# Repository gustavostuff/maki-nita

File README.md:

MakiNeat is a cartridge-based, two-player portable tabletop Arcade. The name comes from _maquinita_ (pronounced very similarly), the Mexican word generally used for an arcade machine. The display is four white 8x8 LED matrices in a 16x16 field. Graphics are 1-bit (LEDs are either ON or OFF).

On a similar spirit as the Magnavox Odyssey and the Vectrex, MakiNeat uses colored, translucent sheets to cover the screen. So the overlay is an extension of the cartridge, part of the game experience. A magnetic marquee runs along the top and the cartridge sits behind it. The [overlays](docs/overlays.md) and [design](docs/design.md) docs cover the sheet and the system netlist.

An AVR128DB28 on a cartridge runs the game and holds the picture (the cartridge is both the system brain and the game data). Four MAX7219 drivers refresh the screen grid.

## Goals

Simple graphics + simple input can still be fun. A stick (and sometimes a button) is all that's needed. Together with cartridges, colored overlays, and a sturdy design, that is the spirit of MakiNeat.

The build is a simple soldering job.

- Parts are through-hole, on a 2.54 mm grid.
- Chips sit in sockets, so a bad one can be swapped.
- Wires leave the board on headers. Two for player controls, another one for power/reset, and one more for the speaker.

Parts are cheap.

- The main system board is a two-layer 100x100 mm board (~5 USD + shipping). The cartridge is an even smaller PCB.
- The screen is four white 8x8 LED matrices (normally less than 1 USD each), and the chips are commonly available (not EOL or NRND).

- Power is any generic/regulated 5 V adapter.

Software is under the MIT License. The hardware design is under the CERN Open Hardware Licence Version 2, Strongly Reciprocal.

## PCBs

Copper tracing is still a WIP for the main PCB, but the full [SKiDL netlist](tools/kicad/main-pcb/skidl/makineat.py) and KiCad files are already under `tools/kicad/main-pcb/` and `tools/kicad/cart-pcb/` (not tested IRL).

Main system PCB, 100x100 mm:

Cartridge PCB, 44x37 mm:

## Game simulator

`tools/sim` is a netlist simulation of the system. The simulator compiles the cartridge's C game code natively on the host to drive the hardware model. This same C code can be directly flashed to the AVR on the cartridge.

SKiDL export writes `tools/kicad/main-pcb/skidl/makineat.net` and updates net classes in `tools/kicad/main-pcb/makineat_v_04.kicad_pro`. See [firmware](docs/firmware.md).

`./sim.sh` opens the UI. The active cart is named in `cart_placed.json`.

## Screen overlay

Physical translucent sheets, placed in front of the white matrix LEDs and status digits, make multi-colored graphics. A single framed overlay holds colored acetate cutouts across both zones, with game labels along the frame:

## Docs

- [Design](docs/design.md) is the system netlist, cart edge, display chain, and audio wiring from SKiDL and KiCad.
- [Firmware](docs/firmware.md) is the game loop, inputs, sound, SDK, and simulator.
- [Overlays](docs/overlays.md) is the colored sheet in front of the field.
- [Future plans](docs/future-plans.md) is the hardware and firmware enhancement roadmap.
- [Status digits](docs/status-digits.md) is the fifth driver and 7-segment display proposal.
- [Driver to matrix pinout](docs/driver_to_matrix_pinout.md) is the MAX7219 and 1088AS LED matrix pinout and activation reference.

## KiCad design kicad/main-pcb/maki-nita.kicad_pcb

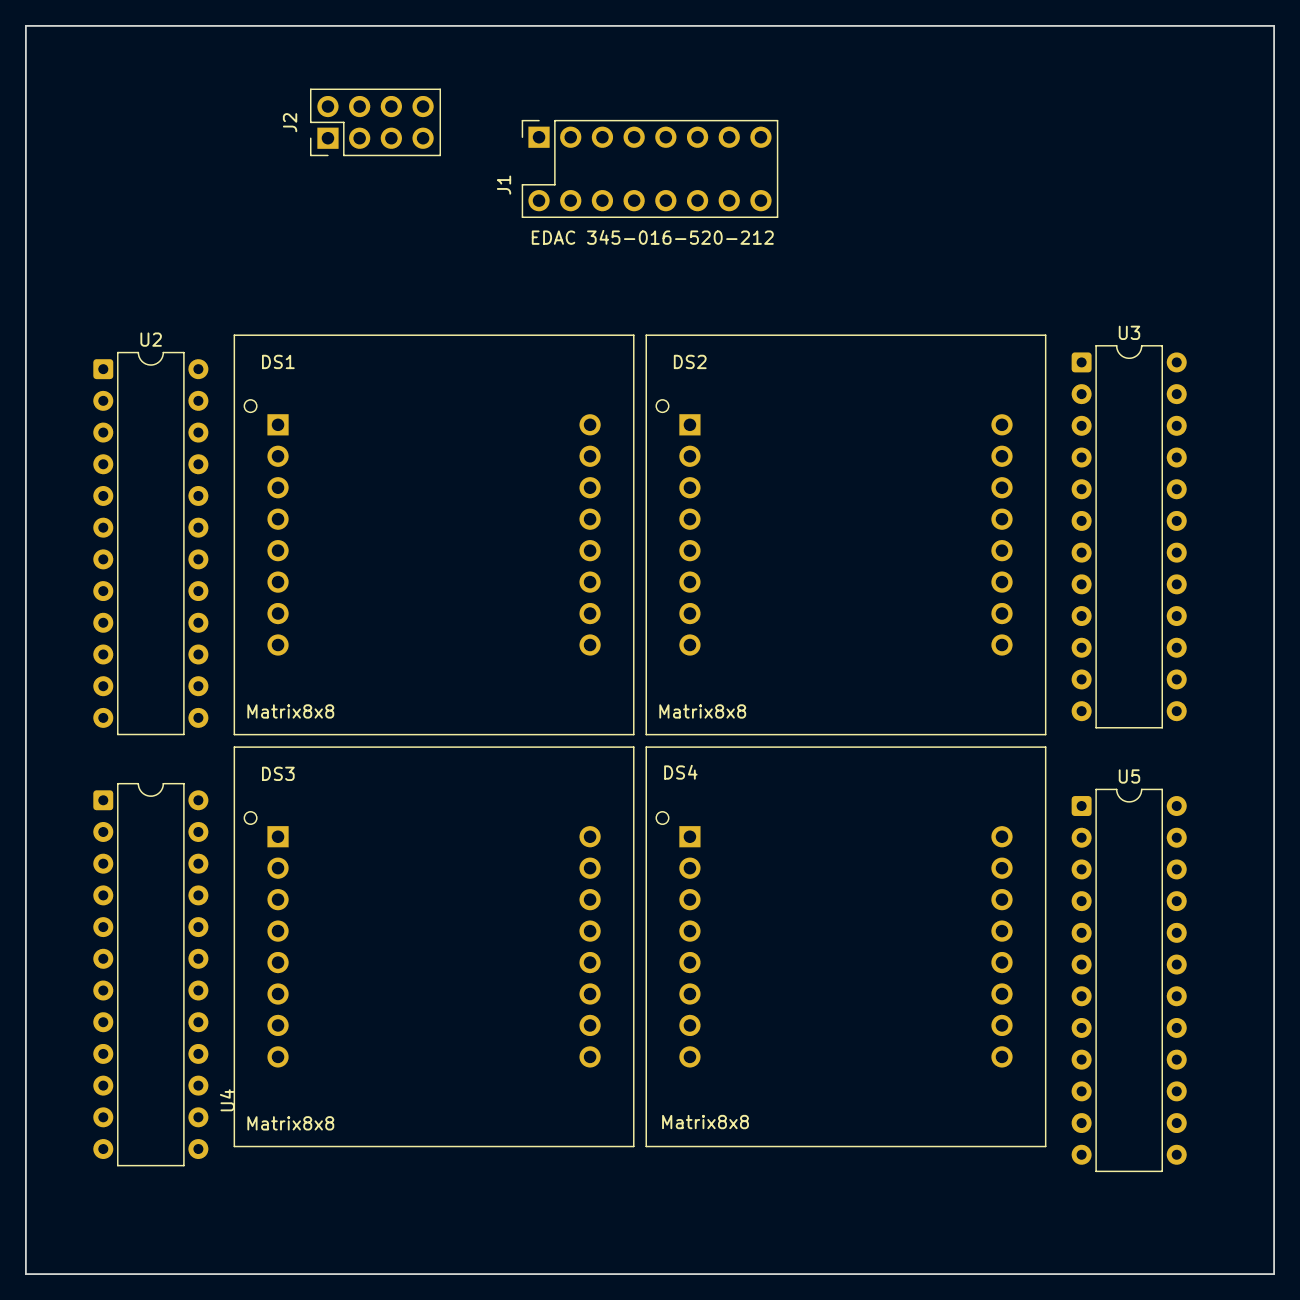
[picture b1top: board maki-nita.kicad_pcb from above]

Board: 2 copper layers, 100.0 x 100.0 mm, 10 parts (0 on the bottom side), 77 nets, no tracks yet.

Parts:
DS1, DS2, DS3, DS4: Matrix8x8; Matrix8x8_2x8_P2.52mm_R25mm
J1: EDAC 345-016-520-212; EDAC_345_MoboSocket_2x8_2.54x5.08mm
J2: PinHeader 2x04; PinHeader_2x04_P2.54mm_Vertical
U2, U3, U4, U5: MAX7219; DIP-24_W7.62mm

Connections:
+5V: J1.3, J1.4, J1.16, J2.2, U2.19, U3.19, U4.19, U5.19
BUTTON: J1.13, J2.7
CLK: J1.10, U2.13, U3.13, U4.13, U5.13
DIN: J1.8, U2.1
DOUT_U2: U2.24, U3.1
DOUT_U3: U3.24, U4.1
DOUT_U4: U4.24, U5.1
DOWN: J1.7, J2.4
GND: J1.1, J1.2, J1.15, J2.1, J2.8, U2.4, U2.9, U3.4, U3.9, U4.4, U4.9, U5.4, U5.9
LEFT: J1.9, J2.5
LOAD: J1.6, U2.12, U3.12, U4.12, U5.12
RIGHT: J1.11, J2.6
ROW1_DS1_C0: DS1.1, U2.22
ROW1_DS1_C1: DS1.2, U2.14
ROW1_DS1_C2: DS1.3, U2.16
ROW1_DS1_C3: DS1.4, U2.20
ROW1_DS1_C4: DS1.5, U2.23
ROW1_DS1_C5: DS1.6, U2.21
ROW1_DS1_C6: DS1.7, U2.15
ROW1_DS1_C7: DS1.8, U2.17
ROW1_DS1_R0: DS1.16, U2.2
ROW1_DS1_R1: DS1.15, U2.11
ROW1_DS1_R2: DS1.14, U2.6
ROW1_DS1_R3: DS1.13, U2.7
ROW1_DS1_R4: DS1.12, U2.3
ROW1_DS1_R5: DS1.11, U2.10
ROW1_DS1_R6: DS1.10, U2.5
ROW1_DS1_R7: DS1.9, U2.8
ROW1_DS2_C0: DS2.1, U3.22
ROW1_DS2_C1: DS2.2, U3.14
ROW1_DS2_C2: DS2.3, U3.16
ROW1_DS2_C3: DS2.4, U3.20
ROW1_DS2_C4: DS2.5, U3.23
ROW1_DS2_C5: DS2.6, U3.21
ROW1_DS2_C6: DS2.7, U3.15
ROW1_DS2_C7: DS2.8, U3.17
ROW1_DS2_R0: DS2.16, U3.2
ROW1_DS2_R1: DS2.15, U3.11
ROW1_DS2_R2: DS2.14, U3.6
ROW1_DS2_R3: DS2.13, U3.7
ROW1_DS2_R4: DS2.12, U3.3
ROW1_DS2_R5: DS2.11, U3.10
ROW1_DS2_R6: DS2.10, U3.5
ROW1_DS2_R7: DS2.9, U3.8
ROW2_DS3_C0: DS3.1, U4.22
ROW2_DS3_C1: DS3.2, U4.14
ROW2_DS3_C2: DS3.3, U4.16
ROW2_DS3_C3: DS3.4, U4.20
ROW2_DS3_C4: DS3.5, U4.23
ROW2_DS3_C5: DS3.6, U4.21
ROW2_DS3_C6: DS3.7, U4.15
ROW2_DS3_C7: DS3.8, U4.17
ROW2_DS3_R0: DS3.16, U4.2
ROW2_DS3_R1: DS3.15, U4.11
ROW2_DS3_R2: DS3.14, U4.6
ROW2_DS3_R3: DS3.13, U4.7
ROW2_DS3_R4: DS3.12, U4.3
ROW2_DS3_R5: DS3.11, U4.10
ROW2_DS3_R6: DS3.10, U4.5
ROW2_DS3_R7: DS3.9, U4.8
ROW2_DS4_C0: DS4.1, U5.22
ROW2_DS4_C1: DS4.2, U5.14
ROW2_DS4_C2: DS4.3, U5.16
ROW2_DS4_C3: DS4.4, U5.20
ROW2_DS4_C4: DS4.5, U5.23
ROW2_DS4_C5: DS4.6, U5.21
ROW2_DS4_C6: DS4.7, U5.15
ROW2_DS4_C7: DS4.8, U5.17
ROW2_DS4_R0: DS4.16, U5.2
ROW2_DS4_R1: DS4.15, U5.11
ROW2_DS4_R2: DS4.14, U5.6
ROW2_DS4_R3: DS4.13, U5.7
ROW2_DS4_R4: DS4.12, U5.3
ROW2_DS4_R5: DS4.11, U5.10
ROW2_DS4_R6: DS4.10, U5.5
ROW2_DS4_R7: DS4.9, U5.8
UP: J1.5, J2.3

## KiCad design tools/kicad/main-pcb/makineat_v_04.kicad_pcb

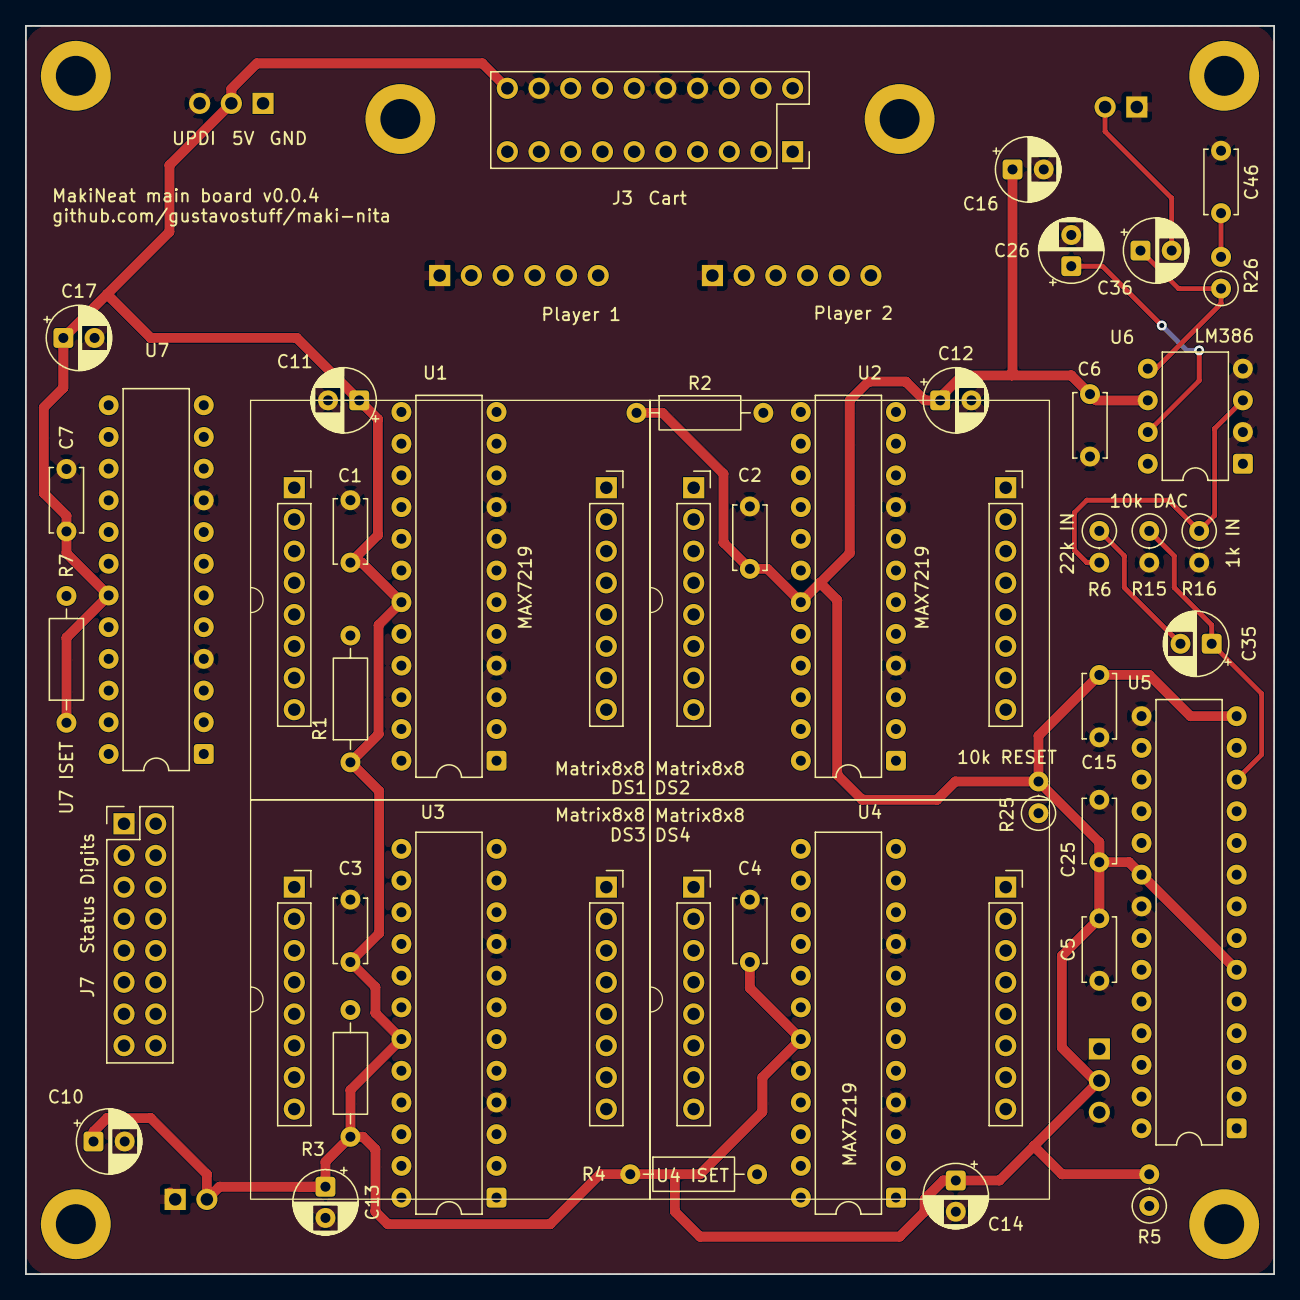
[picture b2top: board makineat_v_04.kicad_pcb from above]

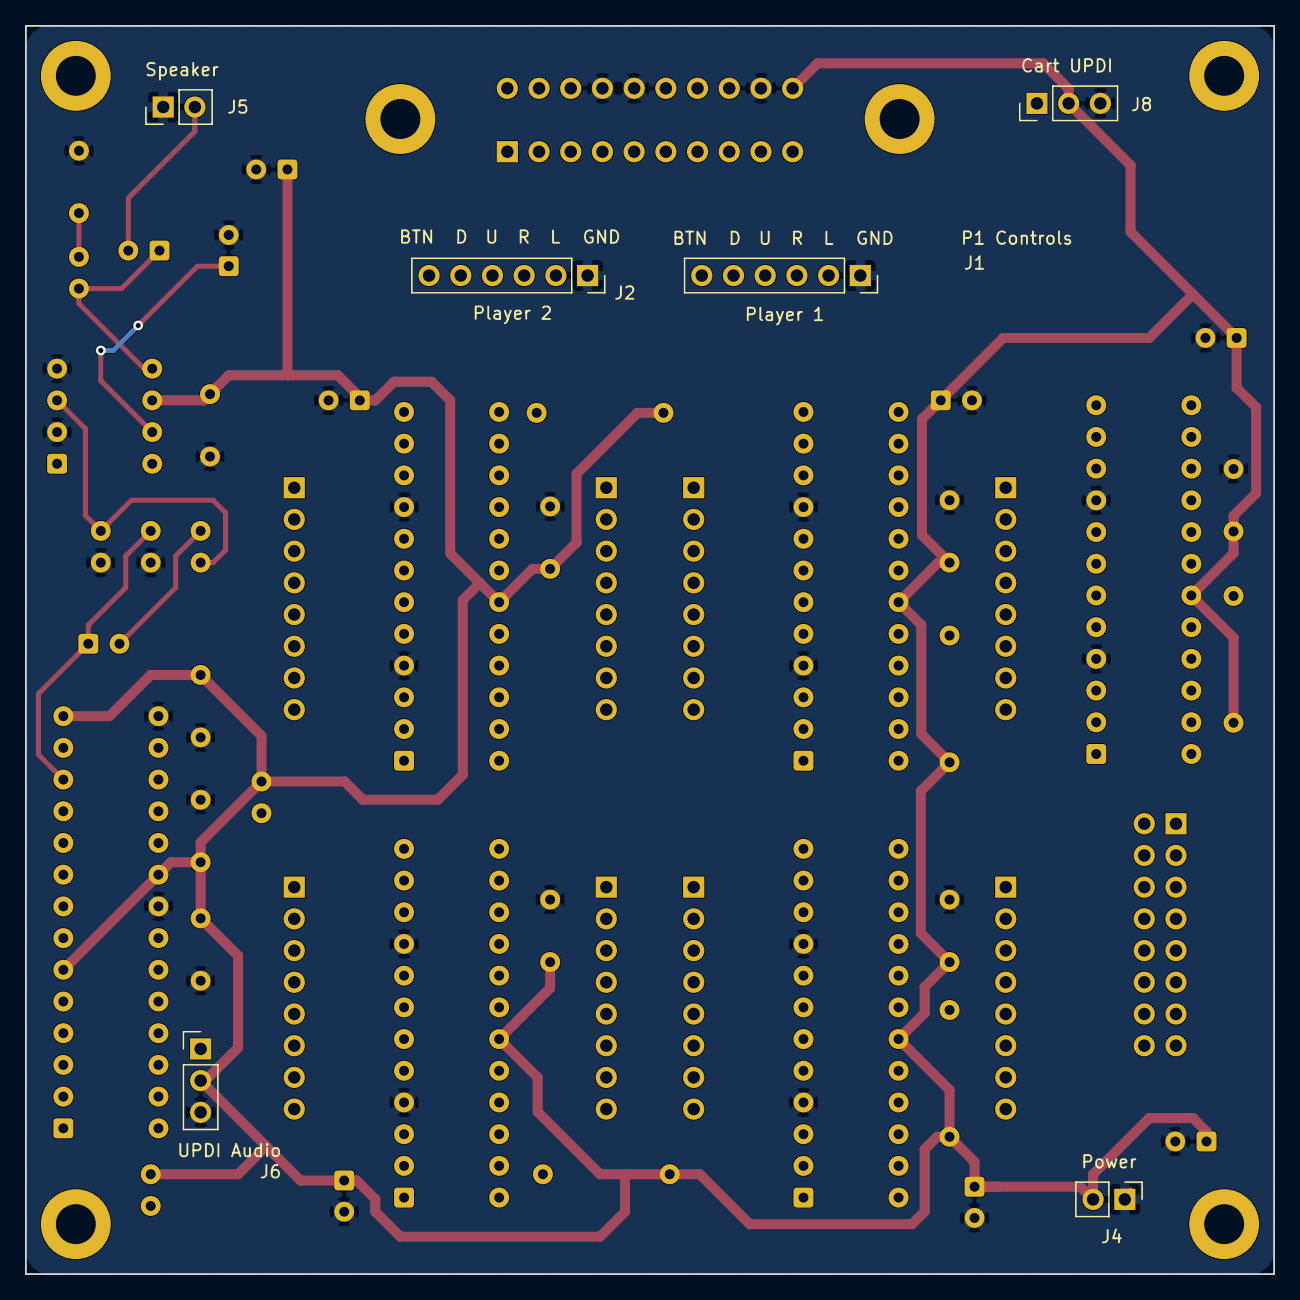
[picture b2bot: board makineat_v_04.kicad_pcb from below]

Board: 2 copper layers, 100.0 x 100.0 mm, 50 parts (6 on the bottom side), 115 nets.

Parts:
C1: U1 V+; C_Disc_D5.0mm_W2.5mm_P5.00mm
C2: U2 V+; C_Disc_D5.0mm_W2.5mm_P5.00mm
C3: U3 V+; C_Disc_D5.0mm_W2.5mm_P5.00mm
C4: U4 V+; C_Disc_D5.0mm_W2.5mm_P5.00mm
C5: U5 VDD; C_Disc_D5.0mm_W2.5mm_P5.00mm
C6: U6 VS; C_Disc_D5.0mm_W2.5mm_P5.00mm
C7: U7 V+; C_Disc_D5.0mm_W2.5mm_P5.00mm
C10: 470u VCC; CP_Radial_D5.0mm_P2.50mm
C11: U1 10u; CP_Radial_D5.0mm_P2.50mm
C12: U2 10u; CP_Radial_D5.0mm_P2.50mm
C13: U3 10u; CP_Radial_D5.0mm_P2.50mm
C14: U4 10u; CP_Radial_D5.0mm_P2.50mm
C15: U5 AVDD; C_Disc_D5.0mm_W2.5mm_P5.00mm
C16: U6 VS; CP_Radial_D5.0mm_P2.50mm
C17: U7 10u; CP_Radial_D5.0mm_P2.50mm
C25: U5 IO; C_Disc_D5.0mm_W2.5mm_P5.00mm
C26: U6 BYP; CP_Radial_D5.0mm_P2.50mm
C35: 1u DAC; CP_Radial_D5.0mm_P2.50mm
C36: 220u SPK; CP_Radial_D5.0mm_P2.50mm
C46: 47n ZOB; C_Disc_D5.0mm_W2.5mm_P5.00mm
DS1, DS2, DS3, DS4: Matrix8x8; Matrix8x8_2x8_P2.52mm_R25mm
J1: P1 Controls; PinHeader_1x06_P2.54mm_Vertical
J2: P2 Controls; PinHeader_1x06_P2.54mm_Vertical
J3: Cart; EDAC_395_MoboSocket_2x10_2.54x5.08mm
J4: Power; PinHeader_1x02_P2.54mm_Vertical
J5: Speaker; PinHeader_1x02_P2.54mm_Vertical
J6: UPDI Audio; PinHeader_1x03_P2.54mm_Vertical
J7: Status Digits; PinHeader_2x08_P2.54mm_Vertical
J8: Cart UPDI; PinHeader_1x03_P2.54mm_Vertical
R1: U1 ISET; R_Axial_DIN0207_L6.3mm_D2.5mm_P10.16mm_Horizontal
R2: U2 ISET; R_Axial_DIN0207_L6.3mm_D2.5mm_P10.16mm_Horizontal
R3: U3 ISET; R_Axial_DIN0207_L6.3mm_D2.5mm_P10.16mm_Horizontal
R4: U4 ISET; R_Axial_DIN0207_L6.3mm_D2.5mm_P10.16mm_Horizontal
R5: 10k EVENT; R_Axial_DIN0207_L6.3mm_D2.5mm_P2.54mm_Vertical
R6: 22k IN; R_Axial_DIN0207_L6.3mm_D2.5mm_P2.54mm_Vertical
R7: U7 ISET; R_Axial_DIN0207_L6.3mm_D2.5mm_P10.16mm_Horizontal
R15: 10k DAC; R_Axial_DIN0207_L6.3mm_D2.5mm_P2.54mm_Vertical
R16: 1k IN; R_Axial_DIN0207_L6.3mm_D2.5mm_P2.54mm_Vertical
R25: 10k RESET; R_Axial_DIN0207_L6.3mm_D2.5mm_P2.54mm_Vertical
R26: 10R ZOB; R_Axial_DIN0207_L6.3mm_D2.5mm_P2.54mm_Vertical
U1, U2, U3, U4, U7: MAX7219; DIP-24_W7.62mm
U5: Audio AVR; DIP-28_W7.62mm
U6: LM386; DIP-8_W7.62mm

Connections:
+5V: C1.1, C2.1, C3.1, C4.1, C5.1, C6.1, C7.1, C10.1, C11.1, C12.1, C13.1, C14.1, C15.1, C16.1, C17.1, C25.1, J3.20, J4.2, J6.2, J8.2, R1.1, R2.1, R3.1, R4.1, R5.2, R7.1, R25.2, U1.19, U2.19, U3.19, U4.19, U5.6, U5.14, U5.20, U6.6, U7.19
AMP: C36.1, R26.1, U6.5
AUD: C35.2, R6.1
AUDIN: R6.2, R16.1, U6.3
AUDIO_UPDI: J6.1, U5.19
BYPASS: C26.1, U6.7
CLK: J3.2, U1.13, U2.13, U3.13, U4.13, U7.13
DAC: C35.1, R15.1, U5.12
DIN: J3.6, U1.1
DOUT_U1: U1.24, U2.1
DOUT_U2: U2.24, U3.1
DOUT_U3: U3.24, U4.1
DOUT_U4: U4.24, U7.1
DS1_0: DS1.0, U1.17
DS1_1: DS1.1, U1.15
DS1_2: DS1.2, U1.11
DS1_3: DS1.3, U1.22
DS1_4: DS1.4, U1.7
DS1_5: DS1.5, U1.21
DS1_6: DS1.6, U1.20
DS1_7: DS1.7, U1.2
DS1_8: DS1.8, U1.3
DS1_9: DS1.9, U1.5
DS1_A: DS1.A, U1.14
DS1_B: DS1.B, U1.16
DS1_C: DS1.C, U1.8
DS1_D: DS1.D, U1.23
DS1_E: DS1.E, U1.10
DS1_F: DS1.F, U1.6
DS2_0: DS2.0, U2.17
DS2_1: DS2.1, U2.15
DS2_2: DS2.2, U2.11
DS2_3: DS2.3, U2.22
DS2_4: DS2.4, U2.7
DS2_5: DS2.5, U2.21
DS2_6: DS2.6, U2.20
DS2_7: DS2.7, U2.2
DS2_8: DS2.8, U2.3
DS2_9: DS2.9, U2.5
DS2_A: DS2.A, U2.14
DS2_B: DS2.B, U2.16
DS2_C: DS2.C, U2.8
DS2_D: DS2.D, U2.23
DS2_E: DS2.E, U2.10
DS2_F: DS2.F, U2.6
DS3_0: DS3.0, U3.17
DS3_1: DS3.1, U3.15
DS3_2: DS3.2, U3.11
DS3_3: DS3.3, U3.22
DS3_4: DS3.4, U3.7
DS3_5: DS3.5, U3.21
DS3_6: DS3.6, U3.20
DS3_7: DS3.7, U3.2
DS3_8: DS3.8, U3.3
DS3_9: DS3.9, U3.5
DS3_A: DS3.A, U3.14
DS3_B: DS3.B, U3.16
DS3_C: DS3.C, U3.8
DS3_D: DS3.D, U3.23
DS3_E: DS3.E, U3.10
DS3_F: DS3.F, U3.6
DS4_0: DS4.0, U4.17
DS4_1: DS4.1, U4.15
DS4_2: DS4.2, U4.11
DS4_3: DS4.3, U4.22
DS4_4: DS4.4, U4.7
DS4_5: DS4.5, U4.21
DS4_6: DS4.6, U4.20
DS4_7: DS4.7, U4.2
DS4_8: DS4.8, U4.3
DS4_9: DS4.9, U4.5
DS4_A: DS4.A, U4.14
DS4_B: DS4.B, U4.16
DS4_C: DS4.C, U4.8
DS4_D: DS4.D, U4.23
DS4_E: DS4.E, U4.10
DS4_F: DS4.F, U4.6
DS5_0: J7.1, U7.17
DS5_1: J7.2, U7.15
DS5_2: J7.3, U7.11
DS5_3: J7.4, U7.22
DS5_4: J7.9, U7.7
DS5_5: J7.10, U7.21
DS5_6: J7.11, U7.20
DS5_7: J7.12, U7.2
DS5_8: J7.5, U7.3
DS5_9: J7.6, U7.5
DS5_A: J7.7, U7.14
DS5_B: J7.8, U7.16
DS5_C: J7.13, U7.8
DS5_D: J7.14, U7.23
DS5_E: J7.15, U7.10
DS5_F: J7.16, U7.6
EVENT: J3.16, R5.1, U5.23
GND: C1.2, C2.2, C3.2, C4.2, C5.2, C6.2, C7.2, C10.2, C11.2, C12.2, C13.2, C14.2, C15.2, C16.2, C17.2, C25.2, C26.2, C46.2, J1.1, J2.1, J3.8, J3.10, J3.18, J4.1, J5.1, J6.3, J8.3, R15.2, R16.2, U1.4, U1.9, U2.4, U2.9, U3.4, U3.9, U4.4, U4.9, U5.15, U5.21, U6.2, U6.4, U7.4, U7.9
LOAD: J3.4, U1.12, U2.12, U3.12, U4.12, U7.12
P1_BTN: J1.6, J3.11
P1_DOWN: J1.5, J3.13
P1_LEFT: J1.2, J3.19
P1_RIGHT: J1.3, J3.17
P1_UP: J1.4, J3.15
P2_BTN: J2.6, J3.1
P2_DOWN: J2.5, J3.3
P2_LEFT: J2.2, J3.9
P2_RIGHT: J2.3, J3.7
P2_UP: J2.4, J3.5
RESET: J3.14, R25.1, U5.18
SPK: C36.2, J5.2
U1_ISET: R1.2, U1.18
U2_ISET: R2.2, U2.18
U3_ISET: R3.2, U3.18
U4_ISET: R4.2, U4.18
U7_ISET: R7.2, U7.18
UPDI: J3.12, J8.1
ZOBEL: C46.1, R26.2

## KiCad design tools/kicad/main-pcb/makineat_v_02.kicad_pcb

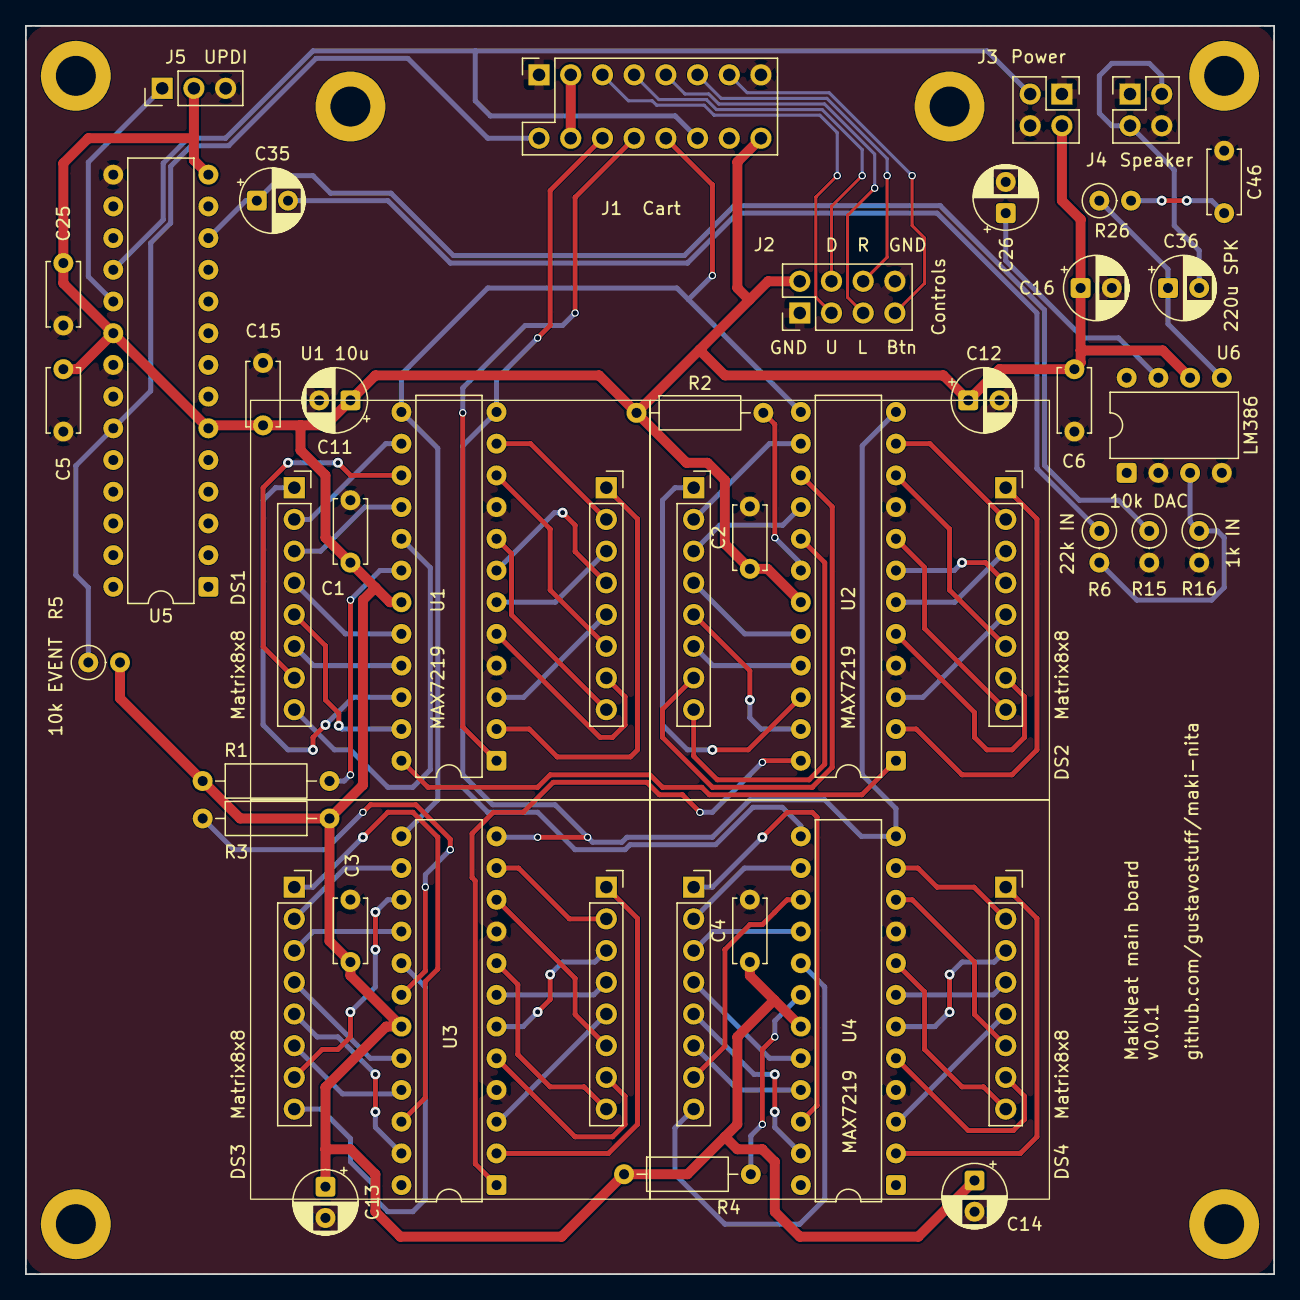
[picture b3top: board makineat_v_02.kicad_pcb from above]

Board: 2 copper layers, 100.0 x 100.0 mm, 41 parts (0 on the bottom side), 91 nets.

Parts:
C1: U1 V+; C_Disc_D5.0mm_W2.5mm_P5.00mm
C2: U2 V+; C_Disc_D5.0mm_W2.5mm_P5.00mm
C3: U3 V+; C_Disc_D5.0mm_W2.5mm_P5.00mm
C4: U4 V+; C_Disc_D5.0mm_W2.5mm_P5.00mm
C5: U5 VDD; C_Disc_D5.0mm_W2.5mm_P5.00mm
C6: U6 VS; C_Disc_D5.0mm_W2.5mm_P5.00mm
C11: U1 10u; CP_Radial_D5.0mm_P2.50mm
C12: U2 10u; CP_Radial_D5.0mm_P2.50mm
C13: U3 10u; CP_Radial_D5.0mm_P2.50mm
C14: U4 10u; CP_Radial_D5.0mm_P2.50mm
C15: U5 AVDD; C_Disc_D5.0mm_W2.5mm_P5.00mm
C16: U6 VS; CP_Radial_D5.0mm_P2.50mm
C25: U5 IO; C_Disc_D5.0mm_W2.5mm_P5.00mm
C26: U6 BYP; CP_Radial_D5.0mm_P2.50mm
C35: 1u DAC; CP_Radial_D5.0mm_P2.50mm
C36: 220u SPK; CP_Radial_D5.0mm_P2.50mm
C46: 47n ZOB; C_Disc_D5.0mm_W2.5mm_P5.00mm
DS1, DS2, DS3, DS4: Matrix8x8; Matrix8x8_2x8_P2.52mm_R25mm
J1: Cart; EDAC_345_MoboSocket_2x8_2.54x5.08mm
J2: Controls; PinHeader_2x04_P2.54mm_Vertical
J3: Power; PinHeader_2x02_P2.54mm_Vertical
J4: Speaker; PinHeader_2x02_P2.54mm_Vertical
J5: UPDI; PinHeader_1x03_P2.54mm_Vertical
R1: U1 ISET; R_Axial_DIN0207_L6.3mm_D2.5mm_P10.16mm_Horizontal
R2: U2 ISET; R_Axial_DIN0207_L6.3mm_D2.5mm_P10.16mm_Horizontal
R3: U3 ISET; R_Axial_DIN0207_L6.3mm_D2.5mm_P10.16mm_Horizontal
R4: U4 ISET; R_Axial_DIN0207_L6.3mm_D2.5mm_P10.16mm_Horizontal
R5: 10k EVENT; R_Axial_DIN0207_L6.3mm_D2.5mm_P2.54mm_Vertical
R6: 22k IN; R_Axial_DIN0207_L6.3mm_D2.5mm_P2.54mm_Vertical
R15: 10k DAC; R_Axial_DIN0207_L6.3mm_D2.5mm_P2.54mm_Vertical
R16: 1k IN; R_Axial_DIN0207_L6.3mm_D2.5mm_P2.54mm_Vertical
R26: 10R ZOB; R_Axial_DIN0207_L6.3mm_D2.5mm_P2.54mm_Vertical
U1, U2, U3, U4: MAX7219; DIP-24_W7.62mm
U5: Audio AVR; DIP-28_W7.62mm
U6: LM386; DIP-8_W7.62mm

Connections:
+5V: C1.1, C2.1, C3.1, C4.1, C5.1, C6.1, C11.1, C12.1, C13.1, C14.1, C15.1, C16.1, C25.1, J1.3, J1.4, J1.16, J2.2, J3.2, J5.2, R1.1, R2.1, R3.1, R4.1, R5.2, U1.19, U2.19, U3.19, U4.19, U5.6, U5.14, U5.20, U6.6
AMP: C36.1, R26.1, U6.5
AUD: C35.2, R6.1
AUDIN: R6.2, R16.1, U6.3
AUDIO_UPDI: J5.1, U5.19
BUTTON: J1.13, J2.7
BYPASS: C26.1, U6.7
CLK: J1.10, U1.13, U2.13, U3.13, U4.13
DAC: C35.1, R15.1, U5.12
DIN: J1.8, U1.1
DOUT_U1: U1.24, U2.1
DOUT_U2: U2.24, U3.1
DOUT_U3: U3.24, U4.1
DOWN: J1.7, J2.4
DS1_C0: DS1.1, U1.22
DS1_C1: DS1.2, U1.14
DS1_C2: DS1.3, U1.16
DS1_C3: DS1.4, U1.20
DS1_C4: DS1.5, U1.23
DS1_C5: DS1.6, U1.21
DS1_C6: DS1.7, U1.15
DS1_C7: DS1.8, U1.17
DS1_R0: DS1.16, U1.2
DS1_R1: DS1.15, U1.11
DS1_R2: DS1.14, U1.6
DS1_R3: DS1.13, U1.7
DS1_R4: DS1.12, U1.3
DS1_R5: DS1.11, U1.10
DS1_R6: DS1.10, U1.5
DS1_R7: DS1.9, U1.8
DS2_C0: DS2.1, U2.22
DS2_C1: DS2.2, U2.14
DS2_C2: DS2.3, U2.16
DS2_C3: DS2.4, U2.20
DS2_C4: DS2.5, U2.23
DS2_C5: DS2.6, U2.21
DS2_C6: DS2.7, U2.15
DS2_C7: DS2.8, U2.17
DS2_R0: DS2.16, U2.2
DS2_R1: DS2.15, U2.11
DS2_R2: DS2.14, U2.6
DS2_R3: DS2.13, U2.7
DS2_R4: DS2.12, U2.3
DS2_R5: DS2.11, U2.10
DS2_R6: DS2.10, U2.5
DS2_R7: DS2.9, U2.8
DS3_C0: DS3.1, U3.22
DS3_C1: DS3.2, U3.14
DS3_C2: DS3.3, U3.16
DS3_C3: DS3.4, U3.20
DS3_C4: DS3.5, U3.23
DS3_C5: DS3.6, U3.21
DS3_C6: DS3.7, U3.15
DS3_C7: DS3.8, U3.17
DS3_R0: DS3.16, U3.2
DS3_R1: DS3.15, U3.11
DS3_R2: DS3.14, U3.6
DS3_R3: DS3.13, U3.7
DS3_R4: DS3.12, U3.3
DS3_R5: DS3.11, U3.10
DS3_R6: DS3.10, U3.5
DS3_R7: DS3.9, U3.8
DS4_C0: DS4.1, U4.22
DS4_C1: DS4.2, U4.14
DS4_C2: DS4.3, U4.16
DS4_C3: DS4.4, U4.20
DS4_C4: DS4.5, U4.23
DS4_C5: DS4.6, U4.21
DS4_C6: DS4.7, U4.15
DS4_C7: DS4.8, U4.17
DS4_R0: DS4.16, U4.2
DS4_R1: DS4.15, U4.11
DS4_R2: DS4.14, U4.6
DS4_R3: DS4.13, U4.7
DS4_R4: DS4.12, U4.3
DS4_R5: DS4.11, U4.10
DS4_R6: DS4.10, U4.5
DS4_R7: DS4.9, U4.8
EVENT: J1.2, R5.1, U5.23
GND: C1.2, C2.2, C3.2, C4.2, C5.2, C6.2, C11.2, C12.2, C13.2, C14.2, C15.2, C16.2, C25.2, C26.2, C46.2, J1.1, J1.15, J2.1, J2.8, J3.1, J3.4, J4.1, J4.4, J5.3, R15.2, R16.2, U1.4, U1.9, U2.4, U2.9, U3.4, U3.9, U4.4, U4.9, U5.15, U5.21, U6.2, U6.4
LEFT: J1.9, J2.5
LOAD: J1.6, U1.12, U2.12, U3.12, U4.12
RESET: J1.12, J3.3, U5.18
RIGHT: J1.11, J2.6
SPK: C36.2, J4.2, J4.3
U1_ISET: R1.2, U1.18
U2_ISET: R2.2, U2.18
U3_ISET: R3.2, U3.18
U4_ISET: R4.2, U4.18
UP: J1.5, J2.3
ZOBEL: C46.1, R26.2

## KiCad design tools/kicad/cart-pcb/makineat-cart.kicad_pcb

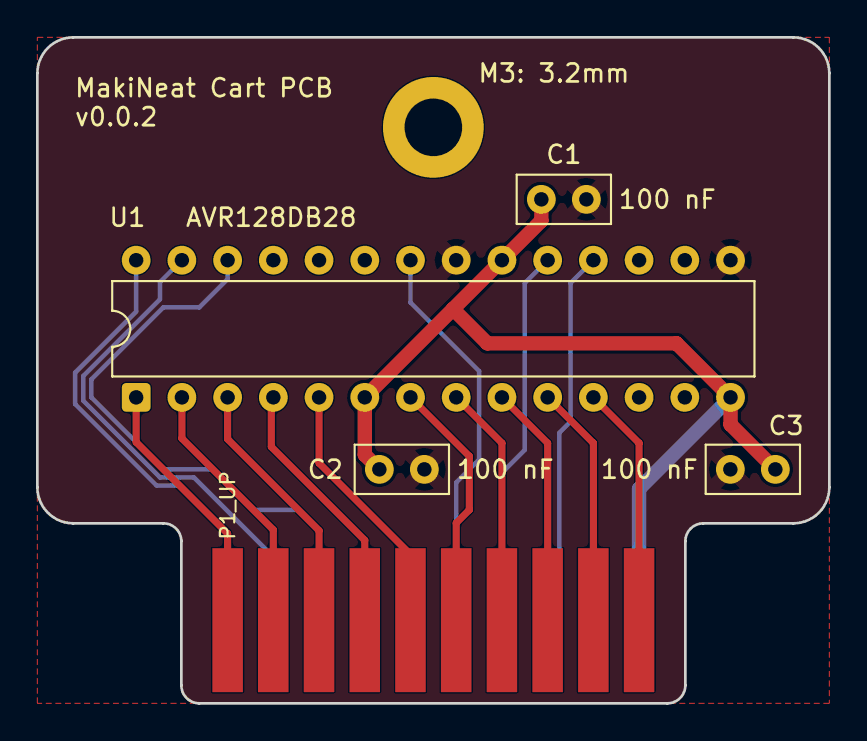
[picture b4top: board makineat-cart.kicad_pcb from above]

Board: 2 copper layers, 44.0 x 37.0 mm, 6 parts (0 on the bottom side), 18 nets.

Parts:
C1, C2, C3: 100 nF; C_Disc_D5.0mm_W2.5mm_P2.50mm
Hole: M3: 3.2mm; MountingHole_3.2mm_M3_DIN965_Pad
J1: Cart edge 2x10; Cart_Edge_2x10_P2.54mm
U1: AVR128DB28; DIP-28_W7.62mm

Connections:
+5V: C1.1, C2.1, C3.1, J1.B10, U1.6, U1.14, U1.20
CLK: J1.B1, U1.28
DIN: J1.B3, U1.26
EVENT: J1.B8, U1.18
GND: C1.2, C2.2, C3.2, J1.B4, J1.B5, J1.B9, U1.15, U1.21
LOAD: J1.B2, U1.27
P1_BTN: J1.A5, U1.5
P1_DOWN: J1.A2, U1.2
P1_LEFT: J1.A3, U1.3
P1_RIGHT: J1.A4, U1.4
P1_UP: J1.A1, U1.1
P2_BTN: J1.A10, U1.11
P2_DOWN: J1.A7, U1.8
P2_LEFT: J1.A8, U1.9
P2_RIGHT: J1.A9, U1.10
P2_UP: J1.A6, U1.7
RESET: J1.B7, U1.19
UPDI: J1.B6, U1.22

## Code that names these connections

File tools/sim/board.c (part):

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    net_tie(&board->vcc, avr_pin(&board->cpu, AVR_VDDIO2));
    net_tie(&board->gnd, avr_pin(&board->cpu, AVR_GND1));
    net_tie(&board->gnd, avr_pin(&board->cpu, AVR_GND2));
    net_tie(&board->din, avr_pin(&board->cpu, AVR_PA4));
    net_tie(&board->clk, avr_pin(&board->cpu, AVR_PA6));
    net_tie(&board->load, avr_pin(&board->cpu, AVR_PA7));
    net_tie(&board->reset, avr_pin(&board->cpu, AVR_PF6));
    net_tie(&board->updi, avr_pin(&board->cpu, AVR_UPDI));
    net_tie(&board->event, avr_pin(&board->cpu, AVR_PA0));
    net_tie(&board->event, avr_pin(&board->audio, AVR_PA1));
    net_tie(&board->vcc, avr_pin(&board->audio, AVR_VDD));
    net_tie(&board->vcc, avr_pin(&board->audio, AVR_AVDD));
    net_tie(&board->vcc, avr_pin(&board->audio, AVR_VDDIO2));
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    net_tie(&board->gnd, avr_pin(&board->audio, AVR_GND2));
    net_tie(&board->reset, avr_pin(&board->audio, AVR_PF6));

    net_tie(&board->din, max7219_pin(&board->drv[0], MAX7219_DIN));
    for (i = 0; i < NDRV; i++)
        tie_chip_rails(board, &board->drv[i]);
    for (i = 0; i < NDRV - 1; i++) {
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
